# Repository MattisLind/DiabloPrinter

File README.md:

# DiabloPrinter

This project is for interfacing the Diablo HyType II Daisy Wheel printer to USB.

[Diablo HyType II](http://www.datormuseum.se/peripherals/diablo-hytype-ii.html)

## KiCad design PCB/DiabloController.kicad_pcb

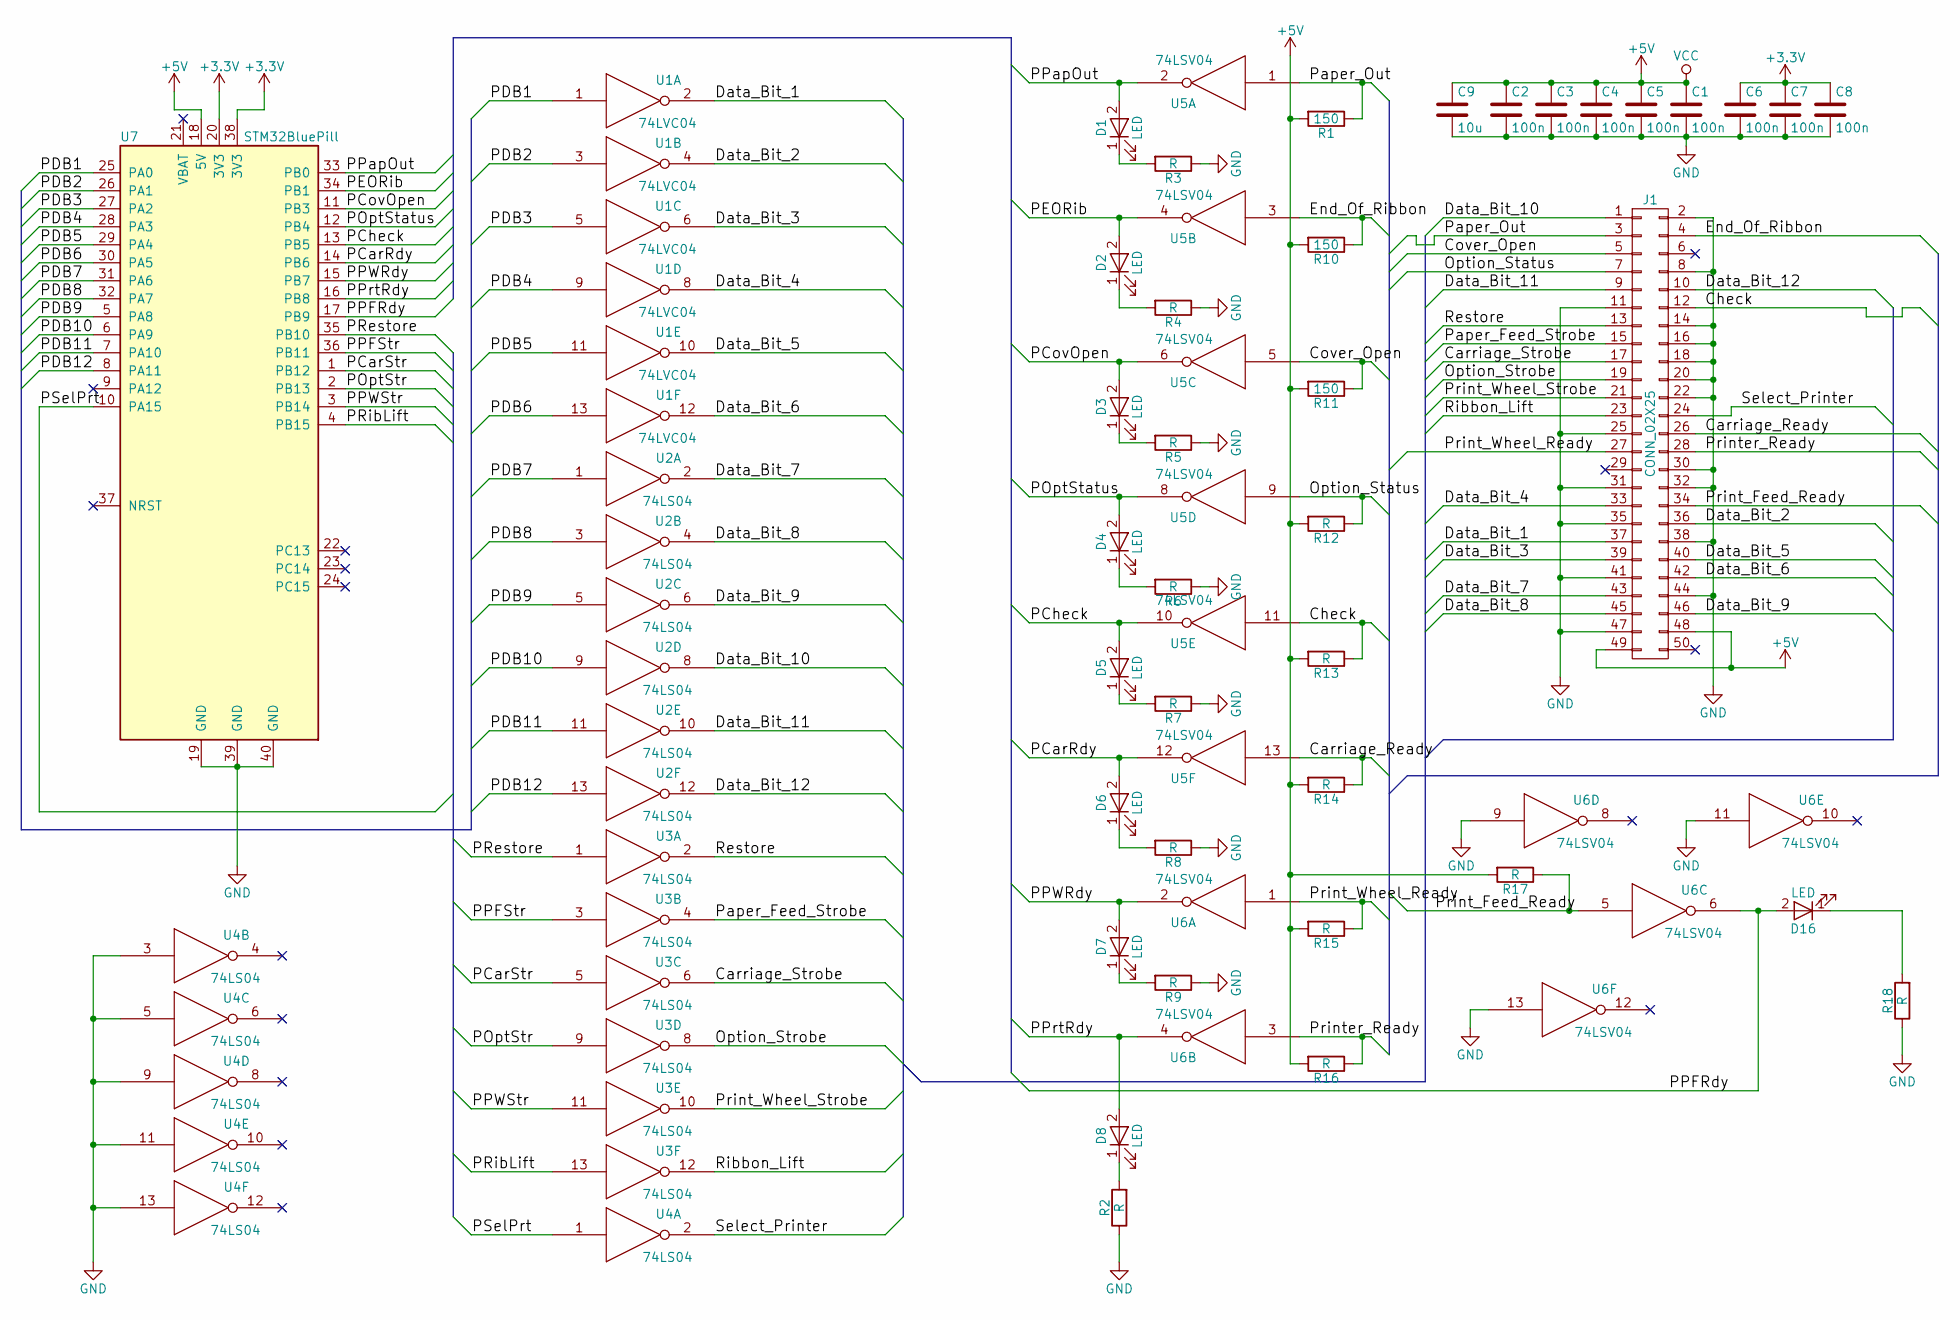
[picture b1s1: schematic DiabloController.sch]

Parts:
C1, C2, C3, C4, C5, C6, C7, C8: 100n; C_0805_HandSoldering
C9: 10u; C_Disc_D5.0mm_W2.5mm_P2.50mm
D1, D2, D3, D4, D5, D6, D7, D8, D16: LED; LED_D3.0mm
J1: CONN_02X25; Pin_Header_Angled_2x25_Pitch2.54mm
R1, R10, R11: 150; R_0805_HandSoldering
R2, R3, R4, R5, R6, R7, R8, R9, R12, R13, R14, R15, R16, R17, R18: R; R_0805_HandSoldering
U1: 74LVC04; SOIC-14_3.9x8.7mm_Pitch1.27mm
U2, U3, U4: 74LS04; SOIC-14_3.9x8.7mm_Pitch1.27mm
U5, U6: 74LSV04; SOIC-14_3.9x8.7mm_Pitch1.27mm
U7: STM32BluePill; DIP-40_W15.24mm_LongPads

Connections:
+3V3: C6.1, C7.1, C8.1, U5.14 (+3V3), U6.14 (+3V3), U7.20 (3V3), U7.38 (3V3)
+5V: C1.1, C2.1, C3.1, C4.1, C5.1, C9.1, J1.48, J1.49, R1.2, R10.2, R11.2, R12.2, R13.2, R14.2, R15.2, R16.2, R17.2, U1.14 (VCC), U2.14 (VCC), U3.14 (VCC), U4.14 (VCC), U7.18 (5V)
/Carriage_Ready: J1.26, R14.1, U5.13
/Carriage_Strobe: J1.17, U3.6
/Check: J1.12, R13.1, U5.11
/Cover_Open: J1.5, R11.1, U5.5
/Data_Bit_1: J1.37, U1.2
/Data_Bit_2: J1.36, U1.4
/Data_Bit_3: J1.39, U1.6
/Data_Bit_4: J1.33, U1.8
/Data_Bit_5: J1.40, U1.10
/Data_Bit_6: J1.42, U1.12
/Data_Bit_7: J1.43, U2.2
/Data_Bit_8: J1.45, U2.4
/Data_Bit_9: J1.46, U2.6
/Data_Bit_10: J1.1, U2.8
/Data_Bit_11: J1.9, U2.10
/Data_Bit_12: J1.10, U2.12
/End_Of_Ribbon: J1.4, R10.1, U5.3
/Option_Status: J1.7, R12.1, U5.9
/Option_Strobe: J1.19, U3.8
/PCarRdy: D6.2 (A), U5.12, U7.14 (PB6)
/PCarStr: U3.5, U7.1 (PB12)
/PCheck: D5.2 (A), U5.10, U7.13 (PB5)
/PCovOpen: D3.2 (A), U5.6, U7.11 (PB3)
/PDB1: U1.1, U7.25 (PA0)
/PDB2: U1.3, U7.26 (PA1)
/PDB3: U1.5, U7.27 (PA2)
/PDB4: U1.9, U7.28 (PA3)
/PDB5: U1.11, U7.29 (PA4)
/PDB6: U1.13, U7.30 (PA5)
/PDB7: U2.1, U7.31 (PA6)
/PDB8: U2.3, U7.32 (PA7)
/PDB9: U2.5, U7.5 (PA8)
/PDB10: U2.9, U7.6 (PA9)
/PDB11: U2.11, U7.7 (PA10)
/PDB12: U2.13, U7.8 (PA11)
/PEORib: D2.2 (A), U5.4, U7.34 (PB1)
/POptStatus: D4.2 (A), U5.8, U7.12 (PB4)
/POptStr: U3.9, U7.2 (PB13)
/PPFRdy: D16.2 (A), U6.6, U7.17 (PB9)
/PPFStr: U3.3, U7.36 (PB11)
/PPWRdy: D7.2 (A), U6.2, U7.15 (PB7)
/PPWStr: U3.11, U7.3 (PB14)
/PPapOut: D1.2 (A), U5.2, U7.33 (PB0)
/PPrtRdy: D8.2 (A), U6.4, U7.16 (PB8)
/PRestore: U3.1, U7.35 (PB10)
/PRibLift: U3.13, U7.4 (PB15)
/PSelPrt: U4.1, U7.10 (PA15)
/Paper_Feed_Strobe: J1.15, U3.4
/Paper_Out: J1.3, R1.1, U5.1
/Print_Feed_Ready: J1.34, R17.1, U6.5
/Print_Wheel_Ready: J1.27, R15.1, U6.1
/Print_Wheel_Strobe: J1.21, U3.10
/Printer_Ready: J1.28, R16.1, U6.3
/Restore: J1.13, U3.2
/Ribbon_Lift: J1.23, U3.12
/Select_Printer: J1.24, U4.2
GND: C1.2, C2.2, C3.2, C4.2, C5.2, C6.2, C7.2, C8.2, C9.2, J1.2, J1.8, J1.11, J1.14, J1.16, J1.18, J1.20, J1.22, J1.25, J1.30, J1.31, J1.32, J1.35, J1.38, J1.41, J1.44, J1.47, R2.1, R3.1, R4.1, R5.1, R6.1, R7.1, R8.1, R9.1, R18.1, U1.7 (GND), U2.7 (GND), U3.7 (GND), U4.3, U4.5, U4.7 (GND), U4.9, U4.11, U4.13, U5.7 (GND), U6.7 (GND), U6.9, U6.11, U6.13, U7.19 (GND), U7.39 (GND), U7.40 (GND)
unnamed: D1.1 (K), R3.2
unnamed: D2.1 (K), R4.2
unnamed: D3.1 (K), R5.2
unnamed: D4.1 (K), R6.2
unnamed: D5.1 (K), R7.2
unnamed: D6.1 (K), R8.2
unnamed: D7.1 (K), R9.2
unnamed: D8.1 (K), R2.2
unnamed: D16.1 (K), R18.2

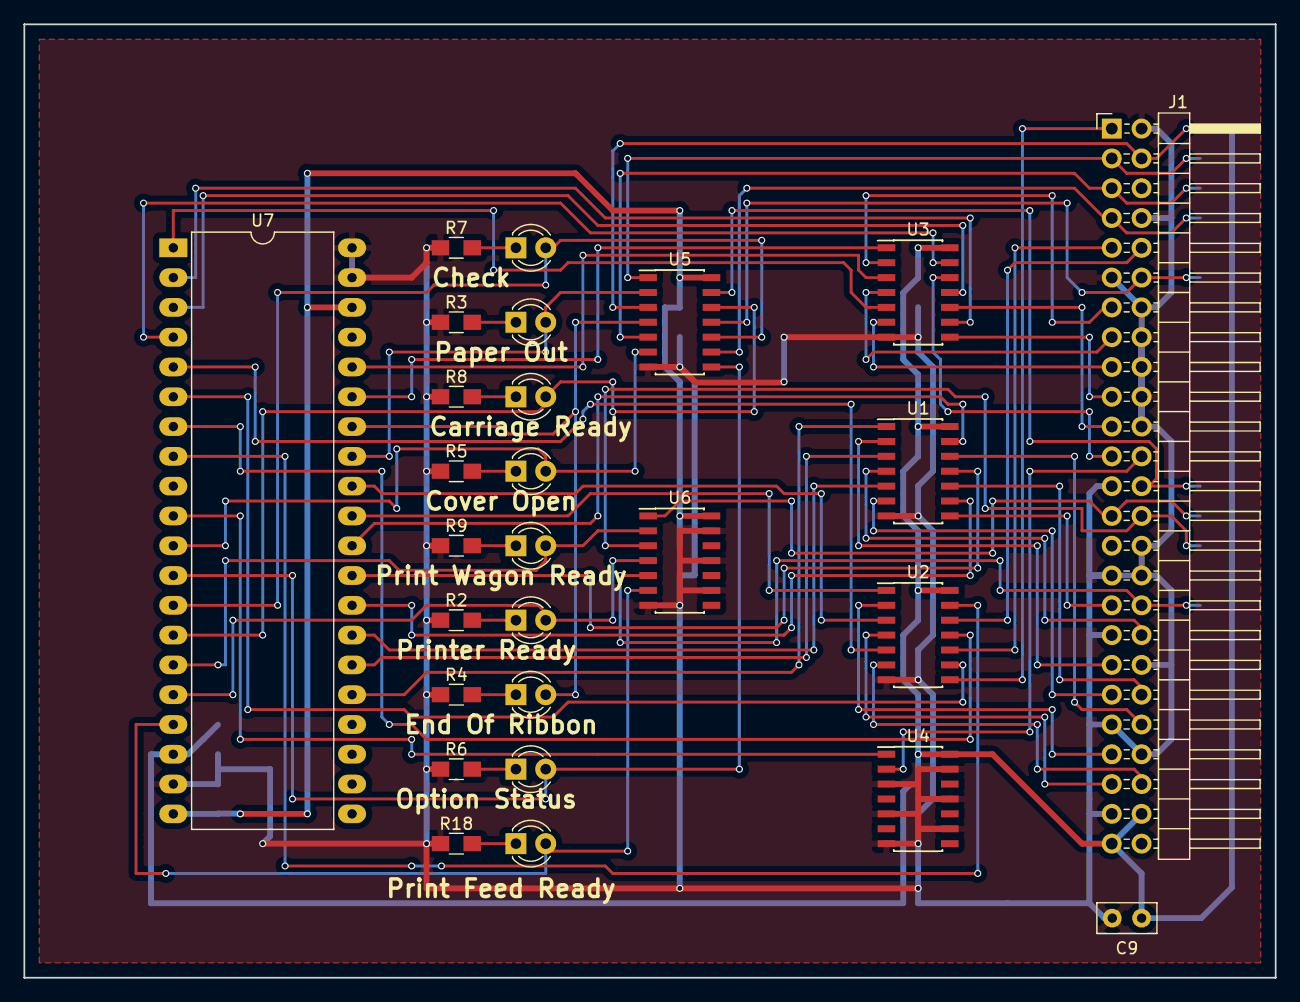
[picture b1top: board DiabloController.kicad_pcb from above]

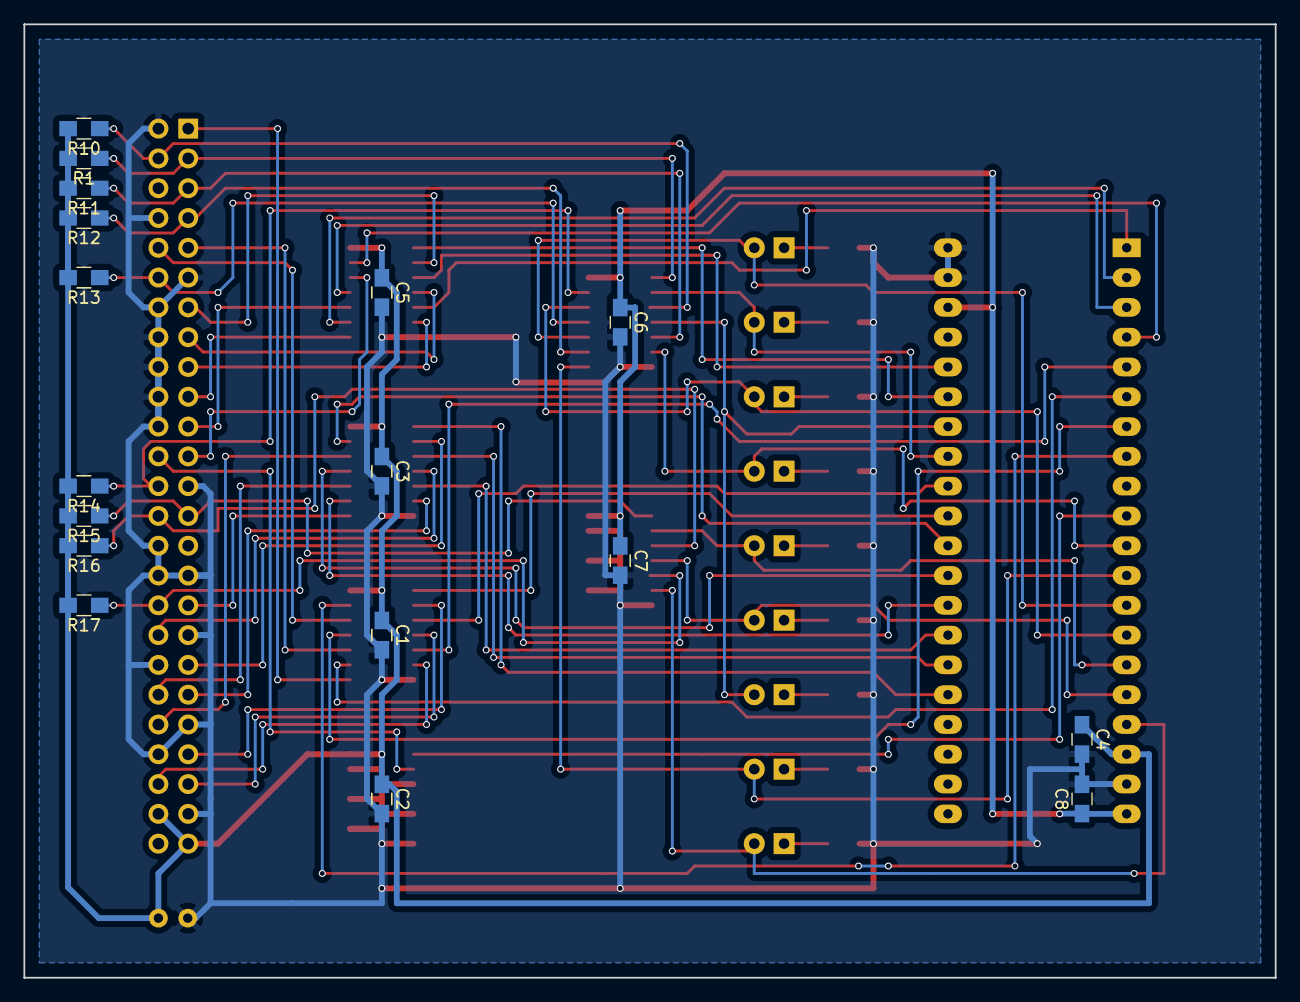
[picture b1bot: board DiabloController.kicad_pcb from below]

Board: 2 copper layers, 106.7 x 81.3 mm, 44 parts (17 on the bottom side), 68 nets.

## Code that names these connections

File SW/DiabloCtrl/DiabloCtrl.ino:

/*
  Blink
  Turns on an LED on for one second, then off for one second, repeatedly.

  Most Arduinos have an on-board LED you can control. On the UNO, MEGA and ZERO 
  it is attached to digital pin 13, on MKR1000 on pin 6. LED_BUILTIN is set to
  the correct LED pin independent of which board is used.
  If you want to know what pin the on-board LED is connected to on your Arduino model, check
  the Technical Specs of your board  at https://www.arduino.cc/en/Main/Products
  
  This example code is in the public domain.

  modified 8 May 2014
  by Scott Fitzgerald
  
  modified 2 Sep 2016
  by Arturo Guadalupi
  
  modified 8 Sep 2016
  by Colby Newman
*/

#define DB1 PA0
#define DB2 PA1
#define DB3 PA2
#define DB4 PA3
#define DB5 PA4
#define DB6 PA5
#define DB7 PA6
#define DB8 PA7
#define DB9 PA8
#define DB10 PA9
#define DB11 PA10
#define DB12 PC13

#define SELECT PA15
#define RIB_LIFT PB15
#define PRT_WHL_STR PB14
#define PRT_OPT_STR PB13
#define PRT_CAR_STR PB12
#define PRT_FEED_STR PB11
#define RESTORE PB10

#define PAP_OUT PB0
#define END_OF_RIB PB1
#define COV_OPEN PB3
#define OPT_STATUS PB4
#define CHECK PB5
#define PRT_CAR_RDY PB6
#define PRT_WHL_RDY PB7
#define PRT_READY PB8
#define PRT_FEED_RDY PB9


String readString;
char select = 0;
char lift=0;


void printUsage() 
{
  Serial.println("S - select, D - Diode, R - Restore, F - Feed, C - Carrige, O - Option, W - Wheel, L - Lift Ribbon");
}

// the setup function runs once when you press reset or power the board
void setup() {
  // initialize digital pin LED_BUILTIN as an output.
  afio_cfg_debug_ports(AFIO_DEBUG_SW_ONLY);
  pinMode(LED_BUILTIN, OUTPUT);
   Serial.begin(9600);
   printUsage();
   Serial.write("DIABLOCTRL> ");
   readString="";
   pinMode(DB1,OUTPUT);
   pinMode(DB2,OUTPUT);
   pinMode(DB3,OUTPUT);
   pinMode(DB4,OUTPUT);
   pinMode(DB5,OUTPUT);
   pinMode(DB6,OUTPUT);
   pinMode(DB7,OUTPUT);
   pinMode(DB8,OUTPUT);
   pinMode(DB9,OUTPUT);
   pinMode(DB10,OUTPUT);
   pinMode(DB11,OUTPUT);
   pinMode(DB12,OUTPUT);
   pinMode(SELECT,OUTPUT);
   pinMode(PAP_OUT,INPUT);
   pinMode(END_OF_RIB,INPUT);
   pinMode(COV_OPEN,INPUT);
   pinMode(OPT_STATUS,INPUT);
   pinMode(CHECK,INPUT);
   pinMode(PRT_CAR_RDY,INPUT);
   pinMode(PRT_WHL_RDY,INPUT);
   pinMode(PRT_READY,INPUT);
   pinMode(PRT_FEED_RDY,INPUT);
   pinMode(RESTORE,OUTPUT);
   pinMode(PRT_FEED_STR,OUTPUT);
   pinMode(PRT_CAR_STR,OUTPUT);
   pinMode(PRT_OPT_STR,OUTPUT);      
   pinMode(PRT_WHL_STR,OUTPUT);
   pinMode(RIB_LIFT,OUTPUT);      
}

void outputDatabits(int bits)
{
  digitalWrite(DB1, (bits & (1<<0))?HIGH:LOW);
  digitalWrite(DB2, (bits & (1<<1))?HIGH:LOW);
  digitalWrite(DB3, (bits & (1<<2))?HIGH:LOW);
  digitalWrite(DB4, (bits & (1<<3))?HIGH:LOW);
  digitalWrite(DB5, (bits & (1<<4))?HIGH:LOW);
  digitalWrite(DB6, (bits & (1<<5))?HIGH:LOW);
  digitalWrite(DB7, (bits & (1<<6))?HIGH:LOW);
  digitalWrite(DB8, (bits & (1<<7))?HIGH:LOW);
  digitalWrite(DB9, (bits & (1<<8))?HIGH:LOW);
  digitalWrite(DB10,(bits & (1<<9))?HIGH:LOW);
  digitalWrite(DB11,(bits & (1<<10))?HIGH:LOW);
  digitalWrite(DB12,(bits & (1<<11))?HIGH:LOW);


}

void printStatus () {
  if (digitalRead(PAP_OUT)) {
    Serial.write("PaperOut ");
  }
  if (digitalRead(END_OF_RIB)) {
    Serial.write("EndOfRibbon ");
  }
  if (digitalRead(COV_OPEN)) {
    Serial.write("CoverOpen ");
  }
  if (digitalRead(OPT_STATUS)) {
    Serial.write("OptionStatus ");
  }
  if (digitalRead(CHECK)) {
    Serial.write("Check ");
  }
  if (digitalRead(PRT_CAR_RDY)) {
    Serial.write("CarriageReady ");
  }
  if (digitalRead(PRT_WHL_RDY)) {
    Serial.write("WheelReady ");
  }
  if (digitalRead(PRT_READY)) {
    Serial.write("PrinterReady ");
  }
  if (digitalRead(PRT_FEED_RDY)) {
    Serial.write("FeedReady ");
  }
  Serial.println("");
}



// the loop function runs over and over again forever
void loop() {
  char c;
  bool cr = false;
  int arg=0;
  
  if(Serial.available()>0) {
    c = Serial.read();
    if (c == '\r') {
      cr = true;
    }
    else { 
      readString.concat(c);
      } 
      Serial.write(c);   
    }
    if (cr) {
      cr = false;
      arg = atoi(readString.substring(1).c_str());
      //Serial.println(readString);
      //Serial.println(readString[0]);
      //Serial.println(arg);
      switch (readString[0]) {
        case 'D':
        case 'd':
        if (arg==1) {
          digitalWrite(LED_BUILTIN, HIGH);   // turn the LED on (HIGH is the voltage level)
          Serial.println("LED on");
        }
        else {
          digitalWrite(LED_BUILTIN, LOW);    // turn the LED off by making the voltage LOW
          Serial.println("LED off");
        }
        break;
        case 'S':
        case 's':
        // toggle select 
          select = 1 - select;
          digitalWrite(SELECT, select);
          break;
        case 'R':
        case 'r':
        // send restore pulse
          digitalWrite(RESTORE, HIGH);
          delay(100);
          digitalWrite(RESTORE, LOW);
          break;
        case 'F':
        case 'f':
          outputDatabits(arg);
          delay(1);
          digitalWrite(PRT_FEED_STR,HIGH);
          delay(1);
          digitalWrite(PRT_FEED_STR,LOW);
          break;
        case 'C':
        case 'c':
          outputDatabits(arg);
          delay(1);
          digitalWrite(PRT_CAR_STR,HIGH);
          delay(1);
          digitalWrite(PRT_CAR_STR,LOW);
          break;
        case 'O':
        case 'o':
          outputDatabits(arg);
          delay(1);
          digitalWrite(PRT_OPT_STR,HIGH);
          delay(1);
          digitalWrite(PRT_OPT_STR,LOW);
          break;
        case 'W':
        case 'w':
          outputDatabits(arg);
          delay(1);
          digitalWrite(PRT_WHL_STR,HIGH);
          delay(1);
          digitalWrite(PRT_WHL_STR,LOW);
          break;
        case 'L':
        case 'l':
        // toggle select 
          lift = 1 - lift;
          digitalWrite(RIB_LIFT, lift);
          //digitalWrite(PA15, lift);
          break;
          
           
      }
      readString="";
      delay(10);
      printStatus();
      printUsage();
      Serial.write("DIABLOCTRL> ");
    }
  }

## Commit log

2018-05-13 Added a README.md file
2018-05-13 Added original version of the PCB without the patches
2018-05-13 Updated schematic for the patches done
2020-07-22 Schematic
2020-07-22 Some components got lost in the move. Fixed automatically by KiCad
2020-07-22 Picture of schematic
2020-07-22 Added schematic
2020-07-22 Added software.
